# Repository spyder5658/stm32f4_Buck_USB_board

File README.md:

# STM32F4-Based 4 layered Board with Dual Power Supply and Protection Features
## Overview
This project showcases a custom STM32F4-based board designed with robust power management and advanced PCB architecture. The board features dual power supply options, reverse polarity protection, a buck converter, and a power indicator LED. Additionally, it boasts a 4-layer PCB design, enhancing signal integrity and ensuring efficient power distribution, making it ideal for high-performance embedded systems.

## Key Features
- Microcontroller: STM32F4 series (ARM Cortex-M4)
- 4-Layer PCB Design:
  - Improved signal integrity and EMI performance.
  - Enhanced power distribution for more stable operation.
- Dual Power Supply Options:
- USB-powered for convenient operation.
- Battery-powered for portable applications.
- Reverse Polarity Protection: Protects the circuit from damage due to incorrect battery polarity.
- Buck Converter: Efficient DC-DC conversion to supply the STM32F4 and other peripherals.
- Power-On LED: Visual indicator to confirm that the board is powered.

## Snapshots

## Applications
- Prototyping and development of embedded systems.
- IoT (Internet of Things) applications requiring reliable power management.
- Low-power, battery-operated devices.
- Educational and research projects on embedded systems.
## Power Supply Details
- USB Power: Provides power through the standard USB connector.
- Battery Power: Connect a battery for portable applications. The board includes a reverse polarity protection circuit to safeguard against incorrect battery connections.
- Buck Converter: The on-board buck converter ensures efficient power delivery, stepping down the battery voltage to the required level for the STM32F4.

## Powering the Board:
Plug in via USB for direct power.
Alternatively, connect a battery (ensure proper polarity).
The Power-On LED will light up if powered correctly.
## Programming the STM32F4:
Use ST-Link or DFU for firmware uploading.
Refer to the STM32CubeIDE Documentation for setting up your development environment.
## Flashing the Firmware:
To flash the firmware onto the STM32F4, use the following:
```
st-flash write firmware.bin 0x08000000
Replace firmware.bin with your compiled binary file.
```

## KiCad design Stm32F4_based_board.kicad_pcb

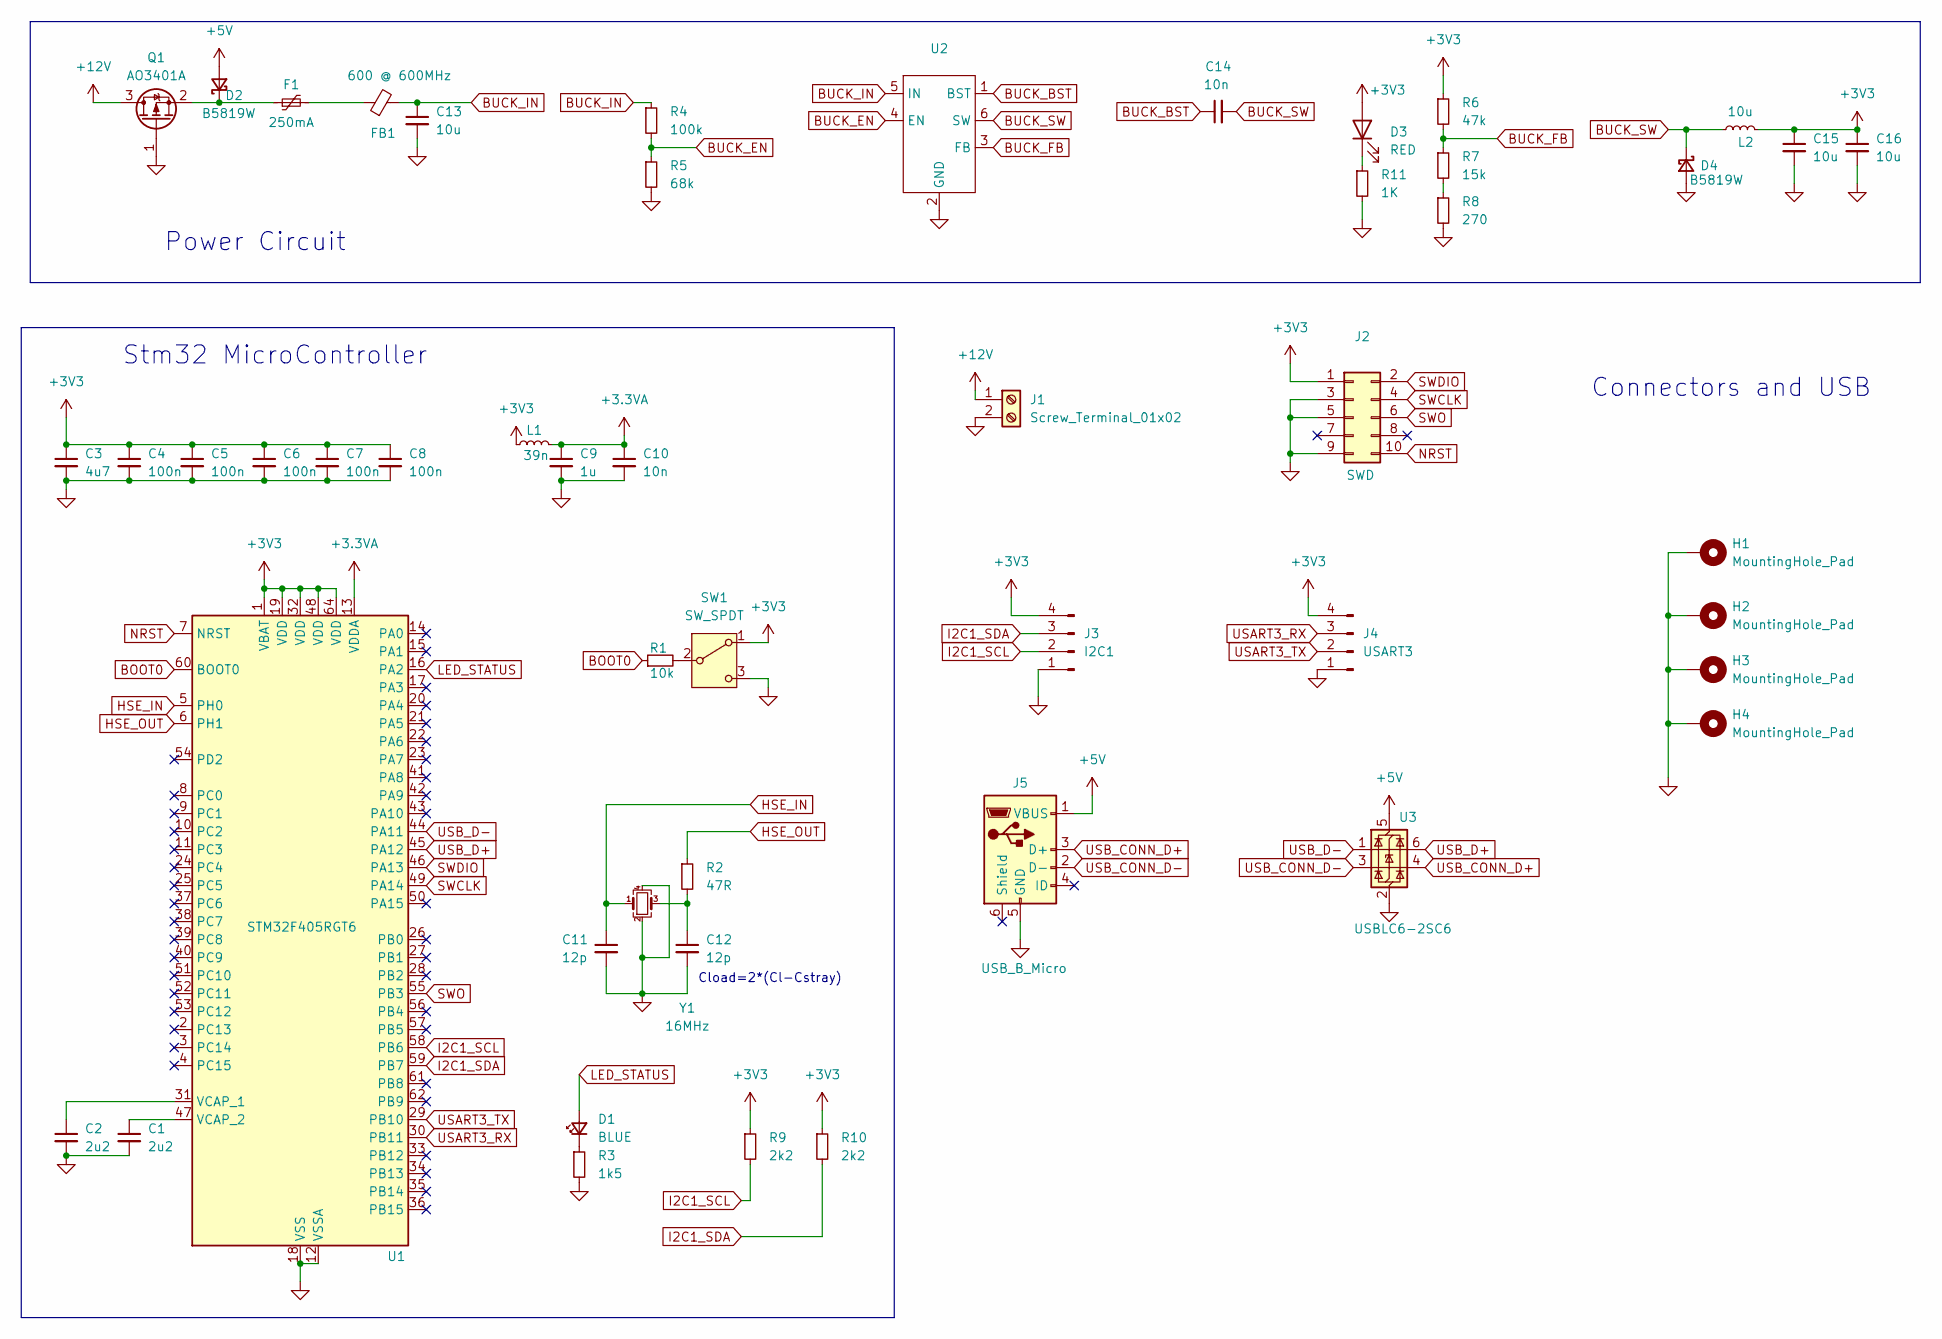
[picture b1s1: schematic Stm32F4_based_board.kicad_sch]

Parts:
C1, C2: 2u2; C_0603_1608Metric
C3: 4u7; C_0603_1608Metric
C4, C5, C6, C7, C8: 100n; C_0402_1005Metric
C9: 1u; C_0402_1005Metric
C10: 10n; C_0402_1005Metric
C11, C12: 12p; C_0402_1005Metric
C13, C15, C16: 10u; C_1206_3216Metric
C14: 10n; C_0603_1608Metric
D1: BLUE; LED_0603_1608Metric
D2, D4: B5819W; D_SOD-123
D3: RED; LED_0603_1608Metric
F1: 250mA; Fuse_1206_3216Metric
FB1: 600 @ 600MHz; L_0805_2012Metric
H1, H2, H3, H4: MountingHole_Pad; MountingHole_4.3mm_M4_Pad_Via
J1: Screw_Terminal_01x02; TerminalBlock_Phoenix_PT-1,5-2-3.5-H_1x02_P3.50mm_Horizontal
J2: SWD; PinSocket_2x05_P1.27mm_Vertical_SMD
J3: I2C1; Molex_PicoBlade_53048-0410_1x04_P1.25mm_Horizontal
J4: USART3; Molex_PicoBlade_53048-0410_1x04_P1.25mm_Horizontal
J5: USB_B_Micro; USB_Micro-B_Wuerth_629105150521
L1: 39n; L_0402_1005Metric
L2: 10u; L_Sunlord_MWSA0518S
Q1: AO3401A; SOT-23
R1: 10k; R_0402_1005Metric
R2: 47R; R_0402_1005Metric
R3: 1k5; R_0603_1608Metric
R4: 100k; R_0603_1608Metric
R5: 68k; R_0603_1608Metric
R6: 47k; R_0603_1608Metric
R7: 15k; R_0603_1608Metric
R8: 270; R_0603_1608Metric
R9, R10: 2k2; R_0402_1005Metric
R11: 1K; R_0603_1608Metric
SW1: SW_SPDT; SW_SPDT_PCM12
U1: STM32F405RGT6; LQFP-64_10x10mm_P0.5mm
U2: SOT-23-6
U3: USBLC6-2SC6; SOT-23-6
Y1: 16MHz; Crystal_SMD_3225-4Pin_3.2x2.5mm

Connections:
+3.3VA: C9.1, C10.1, L1.2, U1.13 (VDDA)
+3V3: C3.1, C4.1, C5.1, C6.1, C7.1, C8.1, C15.1, C16.1, D3.2 (A), J2.1, J3.4, J4.4, L1.1, L2.2, R6.1, R9.1, R10.1, SW1.1 (A), U1.1 (VBAT), U1.19 (VDD), U1.32 (VDD), U1.48 (VDD), U1.64 (VDD)
+5V: D2.2 (A), J5.1 (VBUS), U3.5 (VBUS)
+12V: J1.1, Q1.3 (D)
BOOT0: R1.1, U1.60 (BOOT0)
BUCK_BST: C14.1, U2.1 (BST)
BUCK_EN: R4.2, R5.1, U2.4 (EN)
BUCK_FB: R6.2, R7.1, U2.3 (FB)
BUCK_IN: C13.1, FB1.2, R4.1, U2.5 (IN)
BUCK_SW: C14.2, D4.1 (K), L2.1, U2.6 (SW)
GND: C1.2, C2.2, C3.2, C4.2, C5.2, C6.2, C7.2, C8.2, C9.2, C10.2, C11.2, C12.2, C13.2, C15.2, C16.2, D4.2 (A), H1.1, H2.1, H3.1, H4.1, J1.2, J2.3, J2.5, J2.9, J3.1, J4.1, J5.5 (GND), Q1.1 (G), R3.2, R5.2, R8.2, R11.2, SW1.3 (C), U1.12 (VSSA), U1.18 (VSS), U1.63 (VSS), U2.2 (GND), U3.2 (GND), Y1.2, Y1.4
HSE_IN: C11.1, U1.5 (PH0), Y1.1
HSE_OUT: R2.1, U1.6 (PH1)
I2C1_SCL: J3.2, R9.2, U1.58 (PB6)
I2C1_SDA: J3.3, R10.2, U1.59 (PB7)
LED_STATUS: D1.2 (A), U1.16 (PA2)
NRST: J2.10, U1.7 (NRST)
unnamed: C12.1, R2.2, Y1.3
unnamed: D1.1 (K), R3.1
unnamed: D2.1 (K), F1.1, Q1.2 (S)
unnamed: D3.1 (K), R11.1
unnamed: F1.2, FB1.1
unnamed: R7.2, R8.1
unnamed: R1.2, SW1.2 (B)
unnamed: C2.1, U1.31 (VCAP_1)
unnamed: C1.1, U1.47 (VCAP_2)
SWCLK: J2.4, U1.49 (PA14)
SWDIO: J2.2, U1.46 (PA13)
SWO: J2.6, U1.55 (PB3)
USART3_RX: J4.3, U1.30 (PB11)
USART3_TX: J4.2, U1.29 (PB10)
USB_CONN_D+: J5.3 (D+), U3.4 (I/O2)
USB_CONN_D-: J5.2 (D-), U3.3 (I/O2)
USB_D+: U1.45 (PA12), U3.6 (I/O1)
USB_D-: U1.44 (PA11), U3.1 (I/O1)

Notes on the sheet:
Power Circuit
Stm32 MicroController
Connectors and USB
Cload=2*(Cl-Cstray)

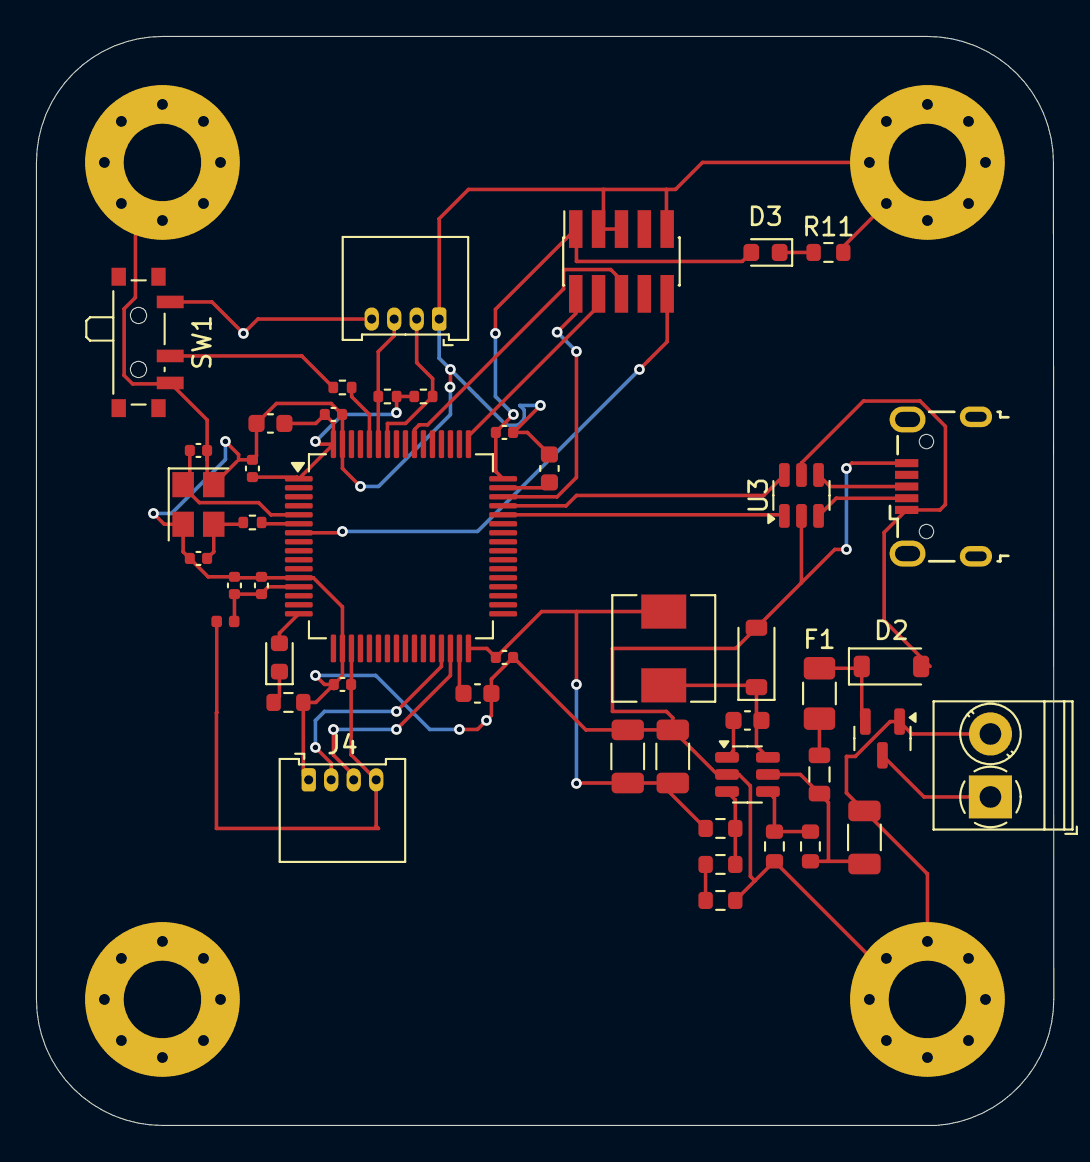
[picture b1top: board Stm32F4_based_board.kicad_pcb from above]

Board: 4 copper layers, 56.5 x 60.5 mm, 50 parts (0 on the bottom side), 35 nets.

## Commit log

2024-10-14 schematic of the stm32f4 based board completed
2024-10-15 updated into PCB with the usb 3d model
